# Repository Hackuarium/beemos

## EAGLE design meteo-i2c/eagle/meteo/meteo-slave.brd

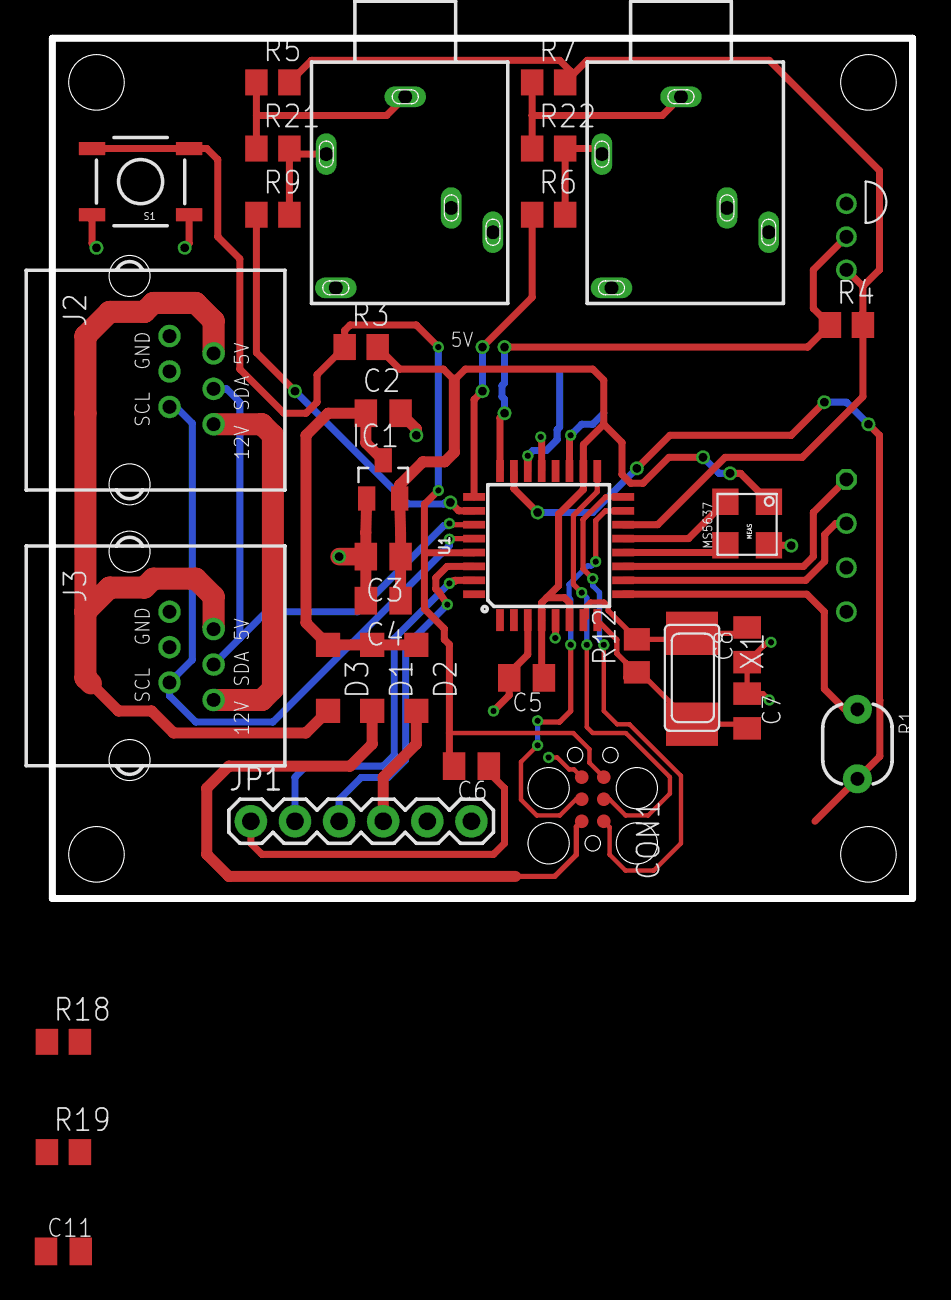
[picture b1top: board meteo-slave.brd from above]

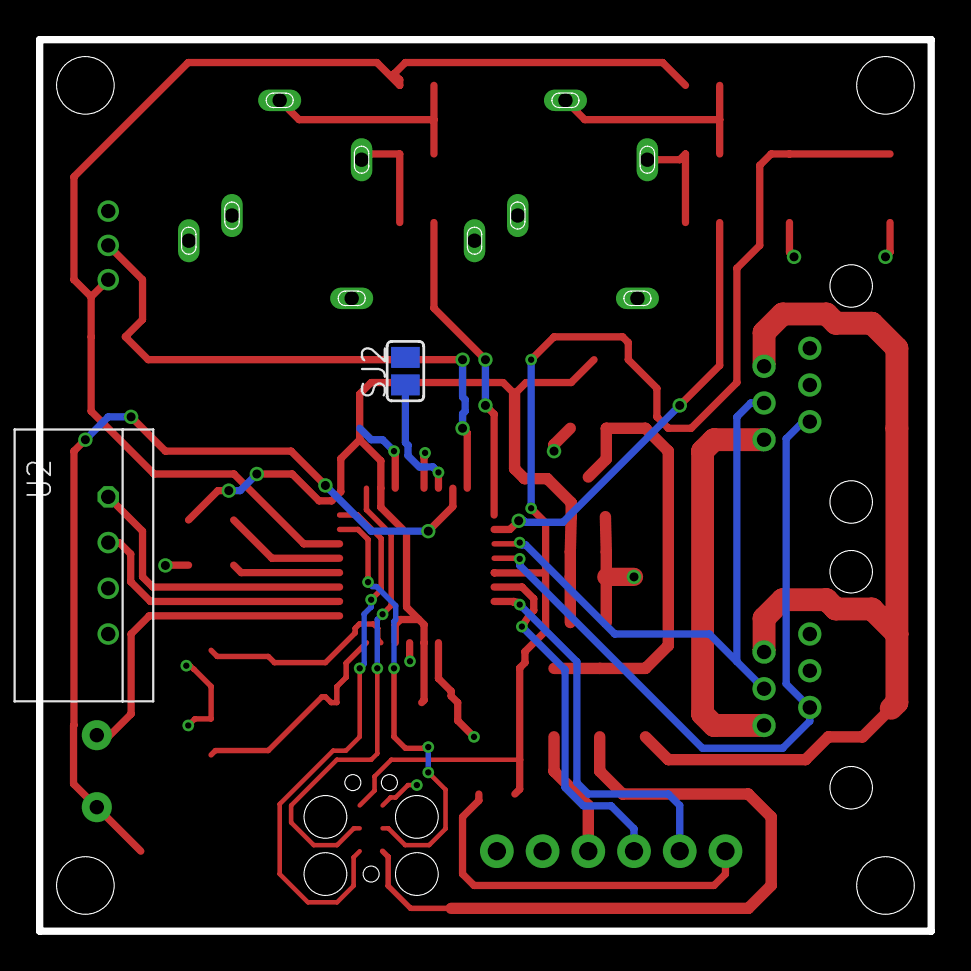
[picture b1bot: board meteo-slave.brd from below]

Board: 2 copper layers, 49.5 x 49.5 mm, 37 parts (2 on the bottom side), 33 nets.

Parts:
C2, C3: 10u; C0805K
C4, C5, C6, C11: 100nF; C0805K
C7, C8: 18pF; C0805K
CON1: SPI; TC2030-MCP
D1, D2, D3: Schottky; SOD123
IC1: MCP1703CB; SOT23
J2, J3: RJ12RIGHTANGLE-I2C; RJ12-RIGHTANGLE-I2C
JP1: FTDI Basic; 1X06
R1: PHOTOCELLPTH; PHOTOCELL
R3: 10k; R0805
R4, R21, R22: 4.7k; R0805
R5, R7: 100; R0805
R6, R9: 1K; R0805
R12, R18: 1M; R0805
R19: 100k; R0805
S1: Reset; TACTILE-SWITCH-SMD-ALT01
SJ2: A1; SJ
U1: ATMEGA328P_TQFP; TQFP32-08
U2: RHT03_DHT-22
U$1: DS1820TO92; DS1820
U$19: MS5637WIDE
X1: 8MHz; NX6035
X2, X3: 1503_09

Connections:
+5V: D3.A, J2.+5V, J3.+5V, R18.2
+12V: J2.+12V, J3.+12V
+XV: C2.1, D1.C, D2.C, D3.C, IC1.3
A0: R1.2, U1.23
A1: R4.1, U1.24, U$1.DQ
A2: R6.1, U1.25
A3: R9.1, U1.26
A6: C11.2, R18.1, R19.2, U1.19
A7: SJ2.1, U1.22
D6: U1.10, U2.DATA
D7: U1.11, U2.VDD
D8: U1.12, U$19.SCL
D9: U1.13, U$19.SDA
D10: R4.2, R5.2, R7.2, U1.14, U$1.VDD
DTR: C6.1, JP1.1
GND: C2.2, C3.2, C4.2, C5.2, C7.1, C8.1, C11.1, CON1.GND, IC1.1, J2.GND1, J2.GND2, J3.GND1, J3.GND2, JP1.5, JP1.6, R1.1, R19.1, S1.1, S1.2, SJ2.2, U1.3, U1.5, U1.21, U2.GND, U$1.GND, U$19.GND, X2.3, X3.3
MISO: CON1.MISO, U1.16
MOSI: CON1.MOSI, U1.15
unnamed: R6.2, R22.2, X3.2
unnamed: R7.1, R22.1, X3.1
unnamed: R5.1, R21.1, X2.1
unnamed: R9.2, R21.2, X2.2
RESET: C6.2, CON1.RESET, R3.1, S1.3, S1.4, U1.29
RX: JP1.3, U1.30
SCK: CON1.SCK, U1.17
SCL: J2.SCL, J3.SCL, U1.28
SDA: J2.SDA, J3.SDA, U1.27
TX: JP1.2, U1.31
VCC: C3.1, C4.1, C5.1, IC1.2, R3.2, U1.4, U1.6, U1.18, U$19.VDD
VCC-FTDI: D2.A, JP1.4
VCC-ICSP: CON1.5V, D1.A
XTAL1: C8.2, R12.2, U1.7, X1.P$2
XTAL2: C7.2, R12.1, U1.8, X1.P$1

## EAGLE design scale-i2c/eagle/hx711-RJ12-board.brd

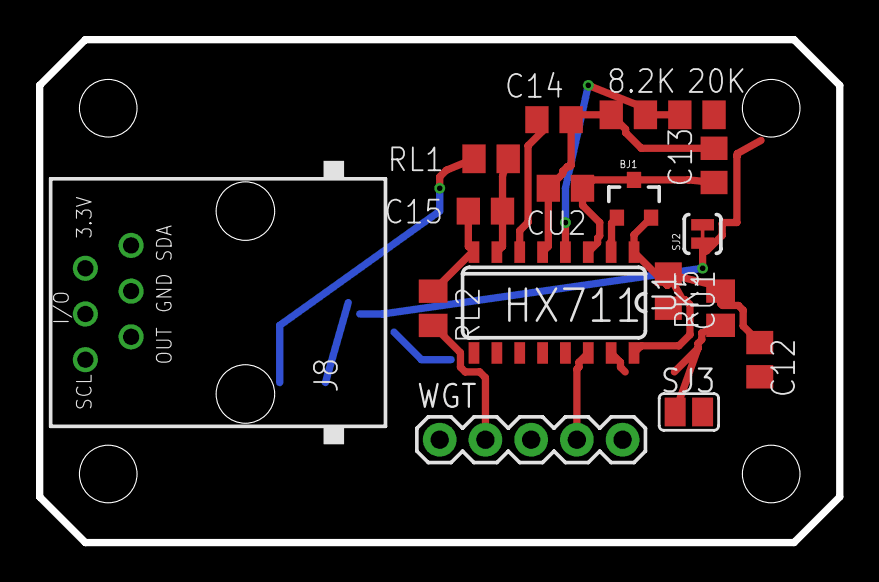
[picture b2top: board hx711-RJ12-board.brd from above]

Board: 2 copper layers, 44.5 x 27.9 mm, 17 parts (0 on the bottom side), 12 nets.

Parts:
8.2K: 8.2k; M0805
20K: 20k; M0805
BJ1: MMBT4403; SOT23-3
C12, C13, C14, C15: 100n; C0805
CU1, CU2: 10u; C0805
J8: RJ123.3; RJ12-STRAIGHT-3.3
RK5: 10k; M0805
RL1, RL2: 100; M0805
SJ2: PAD-JUMPER-2-NC_BY_TRACE_YES_SILK
SJ3: SJ
U1: HX711; SO16
WGT: 1X05

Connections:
3.3V: BJ1.2, C12.1, CU1.1, RK5.2, U1.1, U1.16
A+: RL2.2, WGT.2
A-: RL1.2, WGT.3
CN3: C14.2, U1.6
GND: C12.2, CU1.2, SJ2.1, SJ3.2, U1.14, WGT.1, WGT.4
LGND: 8.2K.1, C13.2, C14.1, CU2.2, SJ2.2, U1.5
unnamed: 20K.2, BJ1.3, C13.1, CU2.1, U1.3, WGT.5
unnamed: C15.2, RL1.1, U1.7
unnamed: BJ1.1, U1.2
unnamed: 8.2K.2, 20K.1, U1.4
unnamed: RK5.1, SJ3.1, U1.15
unnamed: C15.1, RL2.1, U1.8

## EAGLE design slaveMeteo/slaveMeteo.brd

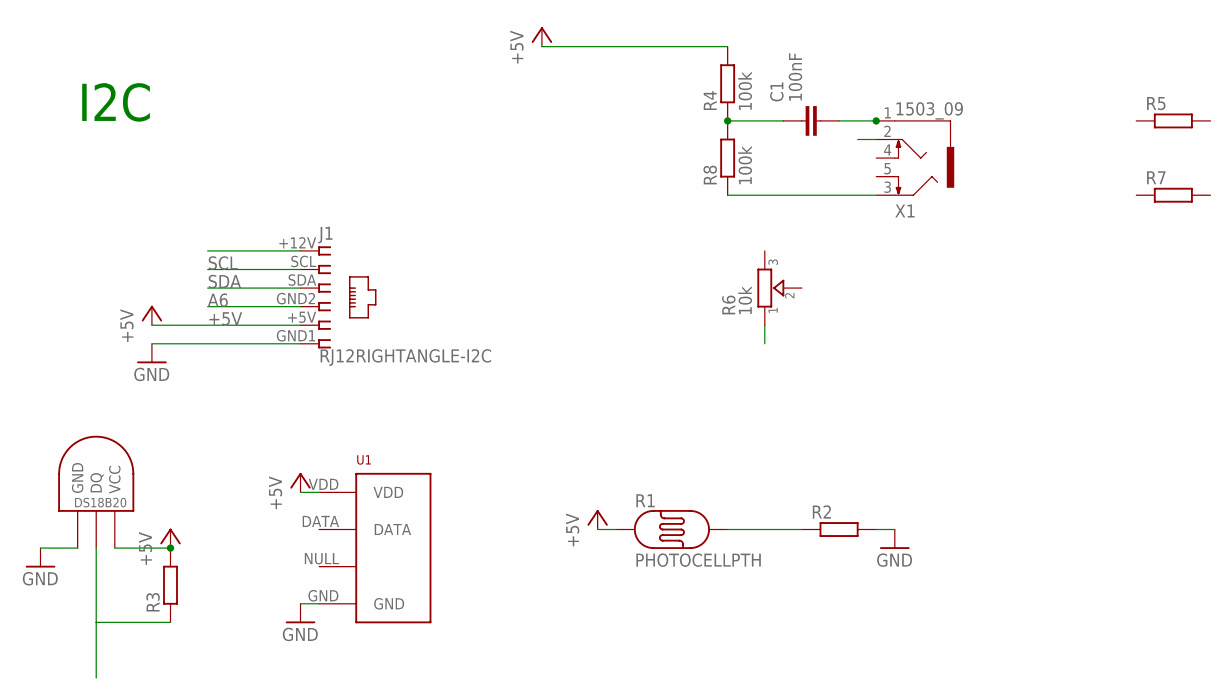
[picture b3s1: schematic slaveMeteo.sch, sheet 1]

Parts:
C1: 100nF; C805
J1: RJ12RIGHTANGLE-I2C; RJ12-RIGHTANGLE-I2C
R1: PHOTOCELLPTH; PHOTOCELL
R2, R3, R5, R7: R-EU_R0805; R0805
R4, R8: 100k; R0805
R6: 10k; TRIMMER_3362P
U1: RHT03_DHT-22_AM2302RA; RHT03_DHT-22/RA
U$1: DS1820TO92; DS1820
X1: 1503_09

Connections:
+5V: J1.+5V (5), R1.1, R3.2, R4.2, U1.VDD, U$1.VDD (VCC)
A6: J1.GND2 (4)
GND: J1.GND1 (6), R2.2, U1.GND, U$1.GND; also elsewhere on the board
GND1: R6.1
GND2: R8.1, X1.3
unnamed: R1.2, R2.1
unnamed: R3.1, U$1.DQ
unnamed: C1.1, R4.1, R8.2
unnamed: C1.2, X1.1
SCL: J1.SCL (2)
SDA: J1.SDA (3)

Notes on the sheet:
I2C

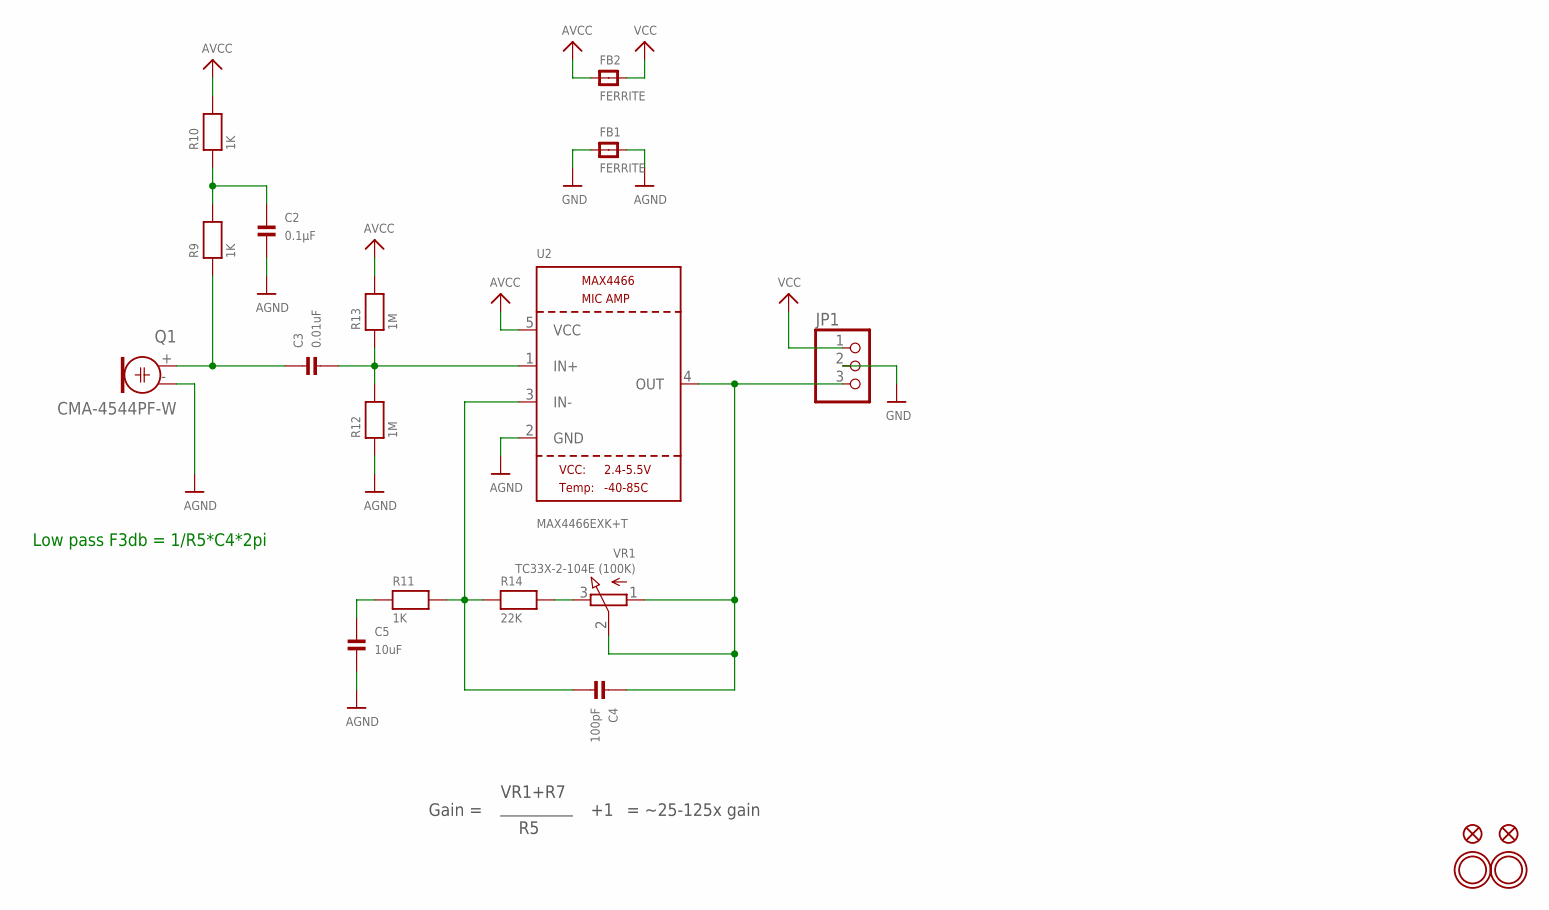
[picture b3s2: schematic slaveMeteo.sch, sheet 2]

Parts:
C2: 0.1µF; 0805
C3: 0.01uF; 0805
C4: 100pF; 0805
C5: 10uF; 0805
FB1, FB2: FERRITE; 0805
FID1, FID2: FIDUCIAL""; FIDUCIAL_1MM
JP1: HEADER-1X376MIL; 1X03_ROUND_76
Q1: CMA-4544PF-W; ELECTRET_9.7
R9, R10, R11: 1K; 0805
R12, R13: 1M; 0805
R14: 22K; 0805
U2: MAX4466EXK+T; SC70-5
U$14, U$15: MOUNTINGHOLE2.5; MOUNTINGHOLE_2.5_PLATED
VR1: TC33X-2-104E (100K); TRIMPOT_BOURNS_TC33X-2

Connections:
AGND: C2.2, C5.2, FB1.2, Q1.- (1), R12.1, U2.2 (GND)
AVCC: FB2.1, R10.2, R13.2, U2.5 (VCC)
GND: FB1.1, JP1.2; also elsewhere on the board
unnamed: C3.1, Q1.+ (2), R9.1
unnamed: C2.1, R9.2, R10.1
unnamed: C3.2, R12.2, R13.1, U2.1 (IN+)
unnamed: C4.1, JP1.3, U2.4 (OUT), VR1.1 (A), VR1.2 (S)
unnamed: C4.2, R11.2, R14.1, U2.3 (IN-)
unnamed: C5.1, R11.1
unnamed: R14.2, VR1.3 (E)
VCC: FB2.2, JP1.1

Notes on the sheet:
Gain =
VR1+R7
= ~25-125x gain
Low pass F3db = 1/R5*C4*2pi

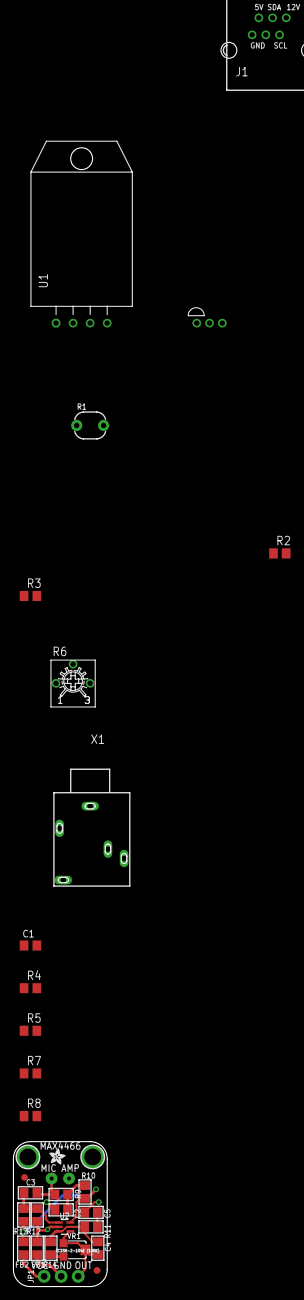
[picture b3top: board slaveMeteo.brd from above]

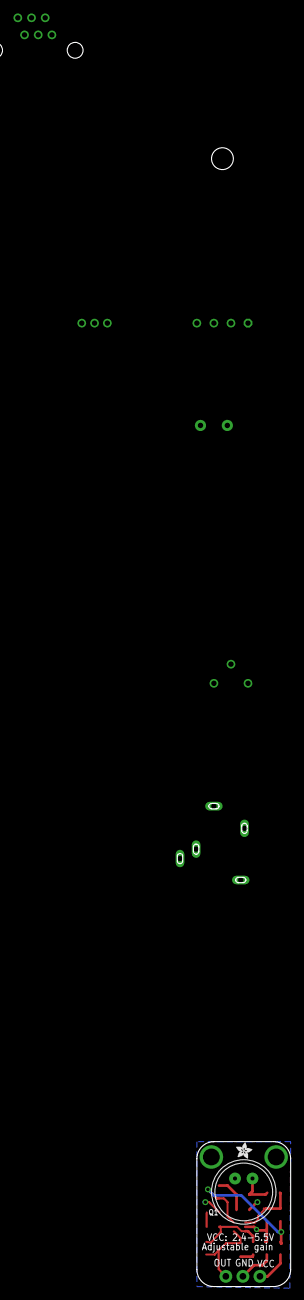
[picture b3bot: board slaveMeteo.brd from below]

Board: 2 copper layers, 35 parts (2 on the bottom side), 17 nets.

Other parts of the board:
U$17, U$18: ADAFRUIT_2.5MM

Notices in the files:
parts and their libraries:
lpatiny: ©2009 ROFA.cz - modified and updated by Robert Darlington ‹rdarlington@gmail.com›
SparkFun-IC-Microcontroller: Licensing: Creative Commons ShareAlike 4.0 International - https://creativecommons.org/licenses/by-sa/4.0
